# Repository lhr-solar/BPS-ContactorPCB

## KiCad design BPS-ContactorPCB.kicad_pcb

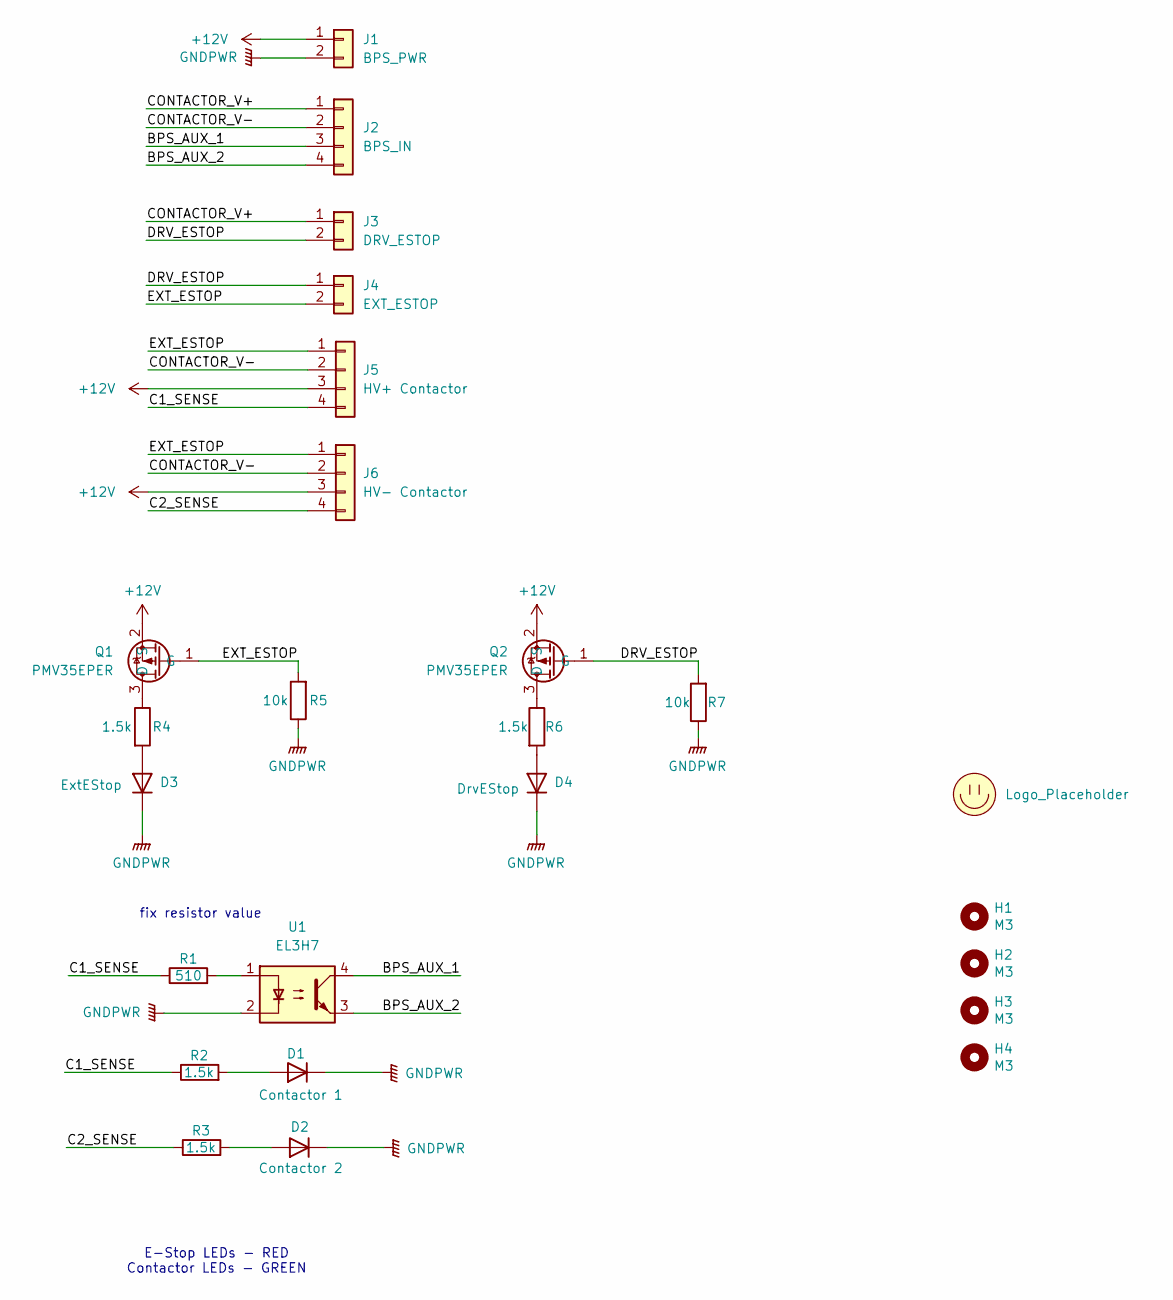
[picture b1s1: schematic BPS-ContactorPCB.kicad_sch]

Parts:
D1: Contactor 1; LED_0805_2012Metric
D2: Contactor 2; LED_0805_2012Metric
D3: ExtEStop; LED_0805_2012Metric
D4: DrvEStop; LED_0805_2012Metric
H1, H2, H3, H4: M3; MountingHole_3mm
J1: BPS_PWR; Molex_MicroFit3.0_1x2xP3.00mm_PolarizingPeg_Vertical
J2: BPS_IN; Molex_MicroFit3.0_1x4xP3.00mm_PolarizingPeg_Vertical
J3: DRV_ESTOP; Molex_MicroFit3.0_1x2xP3.00mm_PolarizingPeg_Vertical
J4: EXT_ESTOP; Molex_MicroFit3.0_1x2xP3.00mm_PolarizingPeg_Vertical
J5: HV+ Contactor; Molex_MicroFit3.0_1x4xP3.00mm_PolarizingPeg_Vertical
J6: HV- Contactor; Molex_MicroFit3.0_1x4xP3.00mm_PolarizingPeg_Vertical
LOGO2: Logo_Placeholder; Hallock_Image_Tiny
Q1, Q2: PMV35EPER; SOT-23
R1: 510; R_0805_2012Metric
R2, R3, R4, R6: 1.5k; R_0805_2012Metric
R5, R7: 10k; R_0805_2012Metric
U1: EL3H7; SOP-4_4.4x2.6mm_P1.27mm

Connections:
+12V: J1.1, J5.3, J6.3, Q1.2 (S), Q2.2 (S)
/BPS_AUX_1: J2.3, U1.4
/BPS_AUX_2: J2.4, U1.3
/C1_SENSE: J5.4, R1.1, R2.1
/C2_SENSE: J6.4, R3.1
/CONTACTOR_V+: J2.1, J3.1
/CONTACTOR_V-: J2.2, J5.2, J6.2
/DRV_ESTOP: J3.2, J4.1, Q2.1 (G), R7.2
/EXT_ESTOP: J4.2, J5.1, J6.1, Q1.1 (G), R5.2
GNDPWR: D1.1 (K), D2.1 (K), D3.1 (K), D4.1 (K), J1.2, R5.1, R7.1, U1.2
unnamed: D1.2 (A), R2.2
unnamed: D2.2 (A), R3.2
unnamed: D3.2 (A), R4.2
unnamed: D4.2 (A), R6.2
unnamed: Q1.3 (D), R4.1
unnamed: Q2.3 (D), R6.1
unnamed: R1.2, U1.1

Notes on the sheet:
fix resistor value
E-Stop LEDs - RED Contactor LEDs - GREEN

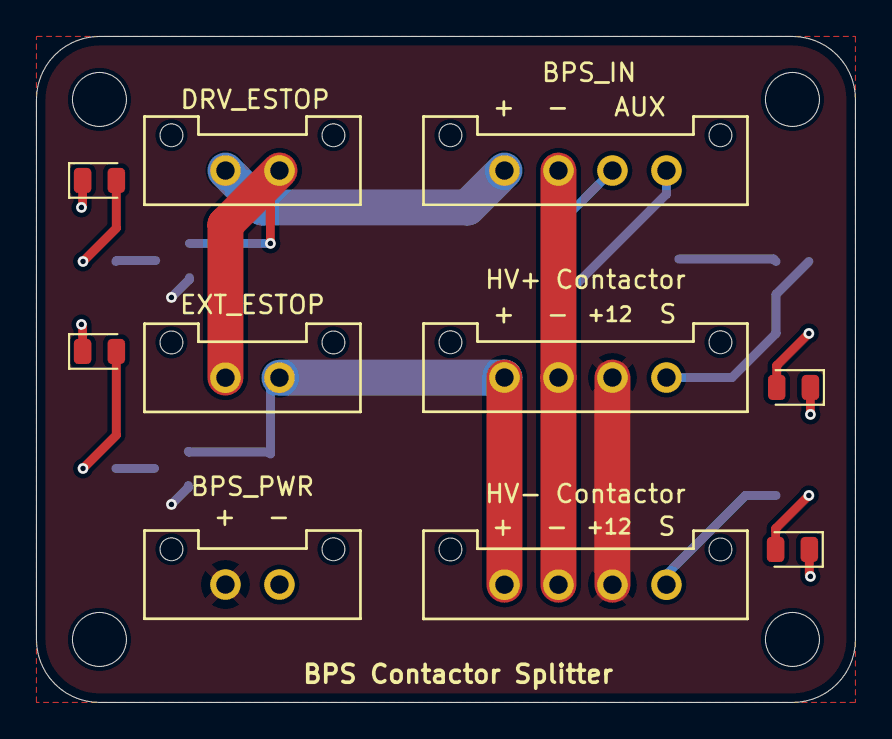
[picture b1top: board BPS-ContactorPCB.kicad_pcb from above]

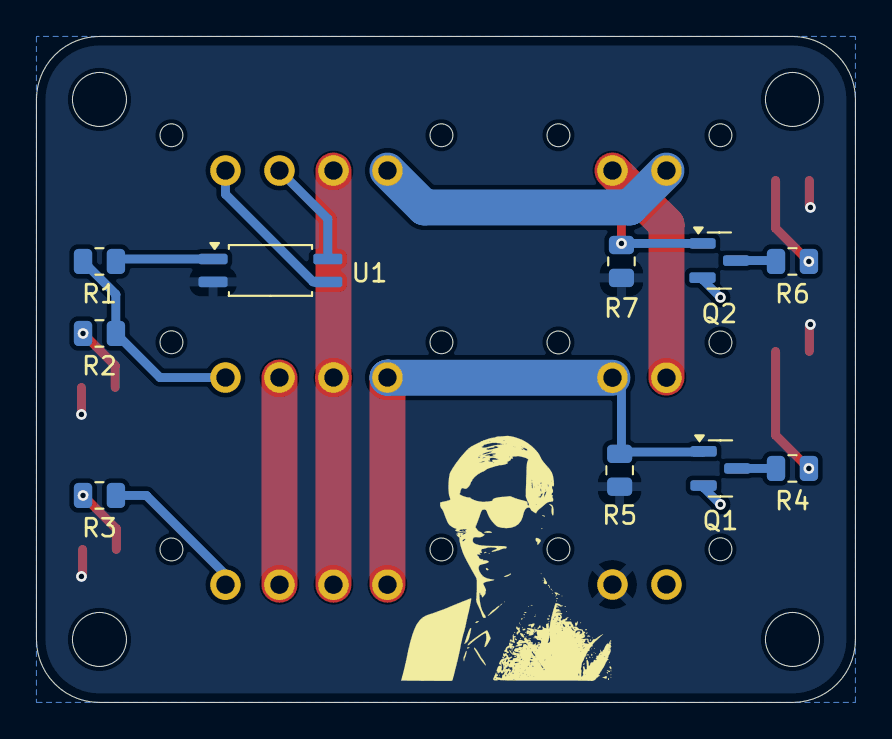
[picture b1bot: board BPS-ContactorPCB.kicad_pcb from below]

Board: 2 copper layers, 45.5 x 37.0 mm, 25 parts (11 on the bottom side), 17 nets.

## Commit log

2024-10-16 done
2024-11-18 Added 2nd ESTOP
2024-11-18 deleted lck files
2024-11-18 Add indicators
2024-11-19 Added green status LEDs for successful contactor close
2024-11-20 contactor status LEDS
2024-11-22 updated layout
2024-11-22 oops. done i hope
2024-11-24 gerbers
